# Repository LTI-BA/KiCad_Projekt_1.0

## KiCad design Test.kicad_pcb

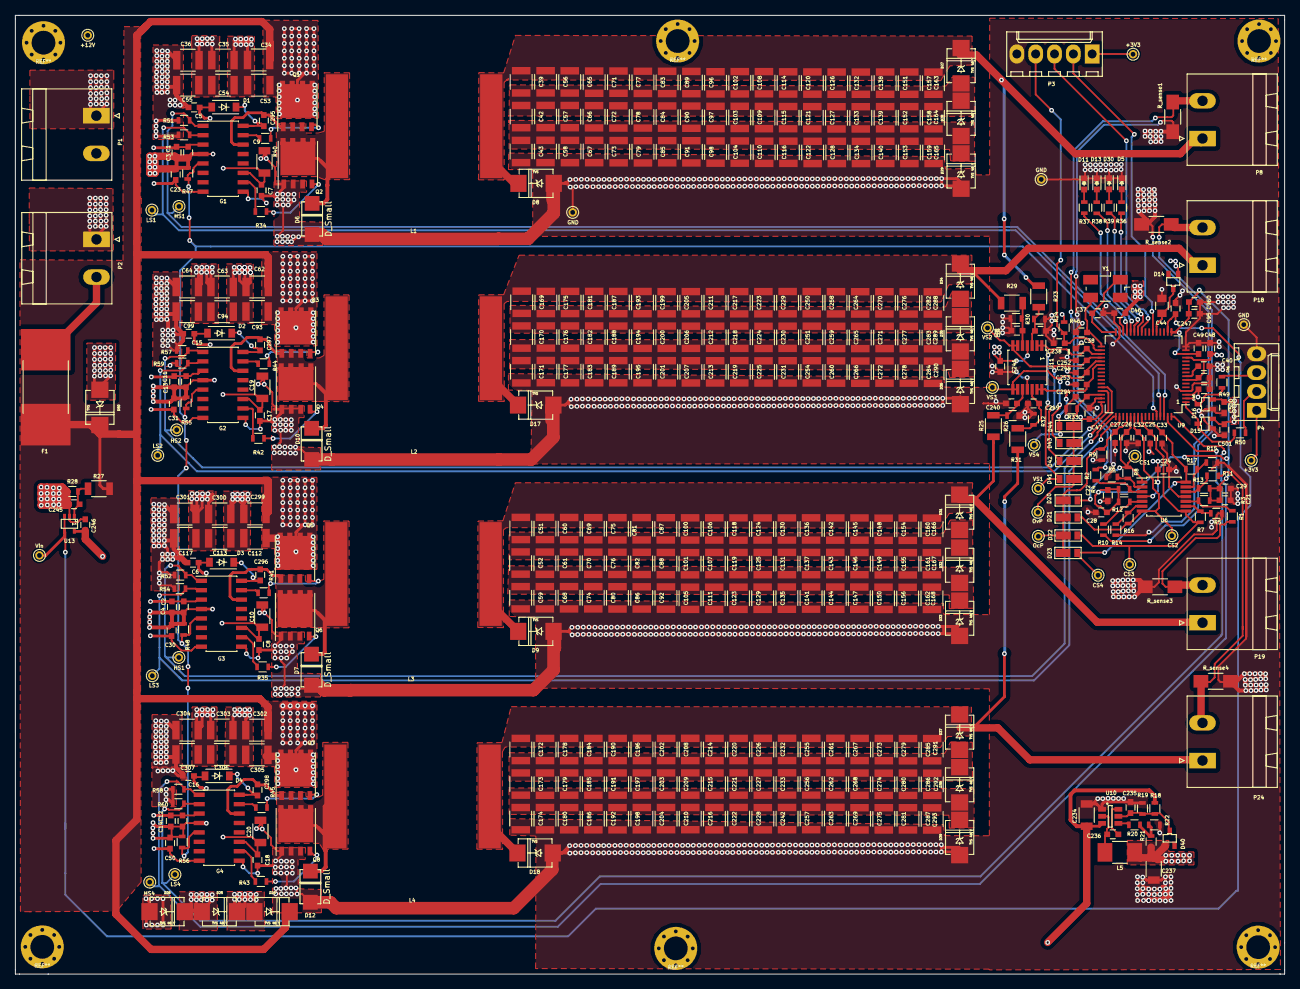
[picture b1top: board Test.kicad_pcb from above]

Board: 4 copper layers, 171.1 x 129.2 mm, 475 parts (0 on the bottom side), 105 nets.

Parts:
+3V3, +3V3#2, +12V: CONN_01X01; PINTST
C1, C2, C5, C6, C11, C12, C15, C16, C40, C41, C236: 1u; C_0603
C3, C4, C7, C8, C13, C14, C17, C18, C23, C24, C27, C30, C31, C45, C46, C47, C48, C49, C50, C95, C235, C238, C241, C246, C294, C295, C296, C297, C298, C500, C501: 100n; C_0603
C9, C10, C19, C20: 10u; C_1206
C21, C22, C28, C29, C239, C240, C245, C248, C249: 100p; C_0603
C25, C26, C32, C33, C243, C244, C247, C252, C253: 33p; C_0603
C34, C35, C36, C39, C42, C43, C51, C52, C53, C54, C55, C56, C57, C58, C59, C60, C61, C62, C63, C64, C65, C66, C67, C68, C69, C70, C71, C72, C73, C74, C75, C76, C77, C78, C79, C80, C81, C82, C83, C84, C85, C86, C87, C88, C89, C90, C91, C92, C93, C94, C96, C97, C98, C99, C100, C101, C102, C103, C104, C105, C106, C107, C108, C109, C110, C111, C112, C113, C114, C115, C116, C117, C118, C119, C120, C121, C122, C123, C124, C125, C126, C127, C128, C129, C130, C131, C132, C133, C134, C135, C136, C137, C138, C139, C140, C141, C142, C143, C144, C145, C146, C147, C148, C149, C150, C151, C152, C153, C154, C155, C156, C157, C158, C159, C160, C161, C162, C163, C164, C165, C166, C167, C168, C169, C170, C171, C172, C173, C174, C175, C176, C177, C178, C179, C180, C181, C182, C183, C184, C185, C186, C187, C188, C189, C190, C191, C192, C193, C194, C195, C196, C197, C198, C199, C200, C201, C202, C203, C204, C205, C206, C207, C208, C209, C210, C211, C212, C213, C214, C215, C216, C217, C218, C219, C220, C221, C222, C223, C224, C225, C226, C227, C228, C229, C230, C231, C232, C233, C242, C250, C251, C254, C255, C256, C257, C258, C259, C260, C261, C262, C263, C264, C265, C266, C267, C268, C269, C270, C271, C272, C273, C274, C275, C276, C277, C278, C279, C280, C281, C282, C283, C284, C285, C286, C287, C288, C289, C290, C291, C292, C293, C299, C300, C301, C302, C303, C304, C305, C306, C307: 10u; C_1210
C37, C38: 18p; C_0603
C44: 47u; C_0805
C234, C237: 22u; C_1206
C960: 10u; C_0603
CS1, CS2, CS3, CS4: CONN_01X01; PINTST
D1, D2, D3, D4: D; SOD-123
D5: red; LED_0603
D6, D7, D10, D12: D_Small; SOD-106
D8, D9, D17, D18: TVS; DO-214AA
D11: yel; LED_0603
D13: grn; LED_0603
D14, D15, D16, D40: BAT54SW; SOT-323
D20, D21, D22, D23, D41, D42, D43, D44: RSX201VA-30; TUMD2
D24, D25, D26, D27, D28, D29, D31, D32, D33, D34, D35, D36, D37, D38, D39: TVS 48 V; DO-214AA_TVS_inp
D30: ble; LED_0603
D50: TVS; DO-214AA_TVS_inp
F1: Fuse; Fuse_462_Serie
G1, G2, G3, G4: Si8237; SOIC-16_3.9x9.9mm_Pitch1.27mm
GND: CONN_01X01; PINTST
GND#2, GND#3: CONN_01X01; PINTST
HS1, HS1#2, HS2, HS4: CONN_01X01; PINTST
L1, L2, L3, L4: 330u; 6000B
L5: 4u7; R_1210_HandSoldering
LS1, LS2, LS3, LS4: CONN_01X01; PINTST
OcP: CONN_01X01; PINTST
OvP: CONN_01X01; PINTST
P1, P2, P8, P18, P19, P24: CONN_01X02; PhoenixContact_MSTBA-G_02x5.08mm_Angled
P3: CONN_01X05; Molex_KK-6410-05_05x2.54mm_Straight
P4: CONN_01X04; Molex_KK-6410-04_04x2.54mm_Straight
Q1, Q2, Q3, Q4, Q5, Q6, Q7, Q8: BSC440N10NS3GATMA1; PG-TDSON-8_F
R1, R2, R10, R11: 68; R_0603
R3, R4, R12, R13: 130k; R_0603
R5, R6, R14, R15, R22: 13k; R_0603
R7, R8, R16, R17: 91k; R_0603
R9, R33, R46, R47, R48, R51, R52, R53, R54, R55, R56, R57, R58, R59, R60: 10k; R_0603
R18: 100k; R_0603
R19: 15k; R_0603
R20: 75k; R_0603
R21: 40k2; R_0603
R23, R25, R27, R29, R31: 1M; R_1206
R24, R26, R28, R30, R32: 7.5k; R_0603
R34, R35, R40, R41, R42, R43, R44, R45: 2; R_0603
R36, R37, R38, R39: 470; R_0603
R49, R50: 22; R_0603
R_sense1, R_sense2, R_sense3, R_sense4: 0.1; R_1206_HandSoldering
U6: TLV4316; TSSOP-14_4.4x5mm_Pitch0.65mm
U9: MK22FN512VLH12; LQFP-64_10x10mm_Pitch0.5mm
U10: AP65201; SOT-23-6
U11: TSV524A; TSSOP-14_4.4x5mm_Pitch0.65mm
U13: TSV521; SC-70-5
VS1, VS2, VS3, VS4: CONN_01X01; PINTST
Vin: CONN_01X01; PINTST
Y1: ABMM2-8.000MHZ-E2-T; Crystal_SMD_5032_4Pads

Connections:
+3V3: +3V3.1, +3V3#2.1, C1.1, C2.1, C3.1, C4.1, C11.1, C12.1, C13.1, C14.1, C23.1, C24.2, C30.1, C31.1, C41.1, C45.2, C46.2, C47.2, C48.2, C50.1, C237.1, C241.1, C246.1, C500.1, C501.1, D14.1, D15.2, D16.2, D40.1, G1.3, G1.8, G2.3, G2.8, G3.3, G3.8, G4.3, G4.8, L5.2, P3.1, P4.1, R21.1, R46.2, U6.4, U9.3, U9.7, U9.13, U9.30, U9.48, U11.4, U13.5
/SW1: C295.2, D6.1, G1.14, L1.1, Q1.1, Q1.2, Q1.3, Q2.5, Q2.6, Q2.7, Q2.8
/SW2: C297.2, D10.1, G2.14, L2.1, Q3.1, Q3.2, Q3.3, Q4.5, Q4.6, Q4.7, Q4.8
/SW3: C296.2, D7.1, G3.14, L3.1, Q5.1, Q5.2, Q5.3, Q6.5, Q6.6, Q6.7, Q6.8
/SW4: C298.2, D12.1, G4.14, L4.1, Q7.1, Q7.2, Q7.3, Q8.5, Q8.6, Q8.7, Q8.8
CMP0_IN1_Overcur_Prot: C27.1, D20.1, D21.1, D22.1, D23.1, OcP.1, R9.1, U9.52
CMP1_IN1_Overvoltage_Prot: C294.1, D41.1, D42.1, D43.1, D44.1, OvP.1, R33.1, U9.46
Curr_Sense_Shunt_1: P8.2, R2.2, R_sense1.1
Curr_Sense_Shunt_2: P18.2, R10.2, R_sense2.1
Curr_Sense_Shunt_3: P19.2, R1.2, R_sense3.1
Curr_Sense_Shunt_4: P24.2, R11.2, R_sense4.1
Disable: G1.5, G2.5, G3.5, G4.5, R47.1, R48.1, R55.1, R56.1, U9.60
GND: C1.2, C2.2, C3.2, C4.2, C5.2, C6.2, C7.2, C8.2, C9.2, C10.2, C11.2, C12.2, C13.2, C14.2, C15.2, C16.2, C17.2, C18.2, C19.2, C20.2, C21.2, C22.2, C23.2, C24.1, C25.2, C26.2, C27.2, C28.2, C29.2, C30.2, C31.2, C32.2, C33.2, C36.2, C37.2, C38.2, C40.2, C41.2, C43.2, C44.2, C45.1, C46.1, C47.1, C48.1, C49.1, C50.2, C55.2, C58.2, C59.2, C64.2, C67.2, C68.2, C73.2, C74.2, C79.2, C80.2, C85.2, C86.2, C91.2, C92.2, C95.2, C98.2, C99.2, C104.2, C105.2, C110.2, C111.2, C116.2, C117.2, C122.2, C123.2, C128.2, C129.2, C134.2, C135.2, C140.2, C141.2, C144.2, C147.2, C150.2, C153.2, C156.2, C159.2, C162.2, C165.2, C168.2, C171.2, C174.2, C177.2, C180.2, C183.2, C186.2, C189.2, C192.2, C195.2, C198.2, C201.2, C204.2, C207.2, C210.2, C213.2, C216.2, C219.2, C222.2, C225.2, C228.2, C231.2, C234.2, C235.2, C237.2, C238.1, C239.2, C240.2, C241.2, C242.2, C243.2, C244.2, C245.2, C246.2, C247.2, C248.2, C249.2, C252.2, C253.2, C254.2, C257.2, C260.2, C263.2, C266.2, C269.2, C272.2, C275.2, C278.2, C281.2, C284.2, C287.2, C290.2, C293.2, C294.2, C301.2, C304.2, C307.2, C500.2, C501.2, C960.2, D5.1, D6.2, D7.2, D8.1, D9.1, D10.2, D11.1, D12.2, D13.1, D15.1, D16.1, D17.1, D18.1, D26.2, D29.2, D30.1, D33.2, D36.2, D39.2, D50.2, G1.4, G1.9, G2.4, G2.9, G3.4, G3.9, G4.4, G4.9, GND.1, GND#2.1, GND#3.1, P1.1, P2.1, P3.5, P4.4, Q2.1, Q2.2, Q2.3, Q4.1, Q4.2, Q4.3, Q6.1, Q6.2, Q6.3, Q8.1, Q8.2, Q8.3, R5.2, R6.2, R9.2, R14.2, R15.2, R19.2, R22.2, R24.2, R26.2, R28.2, R30.2, R32.2, R33.2, R47.2, R48.2, R51.1, R52.1, R53.1, R54.1, R55.2, R56.2, R57.1, R58.1, R59.1, R60.1, R_sense1.2, R_sense2.2, R_sense3.2, R_sense4.2, U6.11, U9.4, U9.15, U9.16, U9.31, U9.47, U10.1, U11.11, U13.2
unnamed: C37.1, U9.32, Y1.1
unnamed: C38.1, U9.33, Y1.2
unnamed: C40.1, U9.8
unnamed: C44.1, D14.3, U9.21
unnamed: C51.2, C52.1, C60.2, C61.1, C69.2, C70.1, C75.2, C76.1, C81.2, C82.1, C87.2, C88.1, C100.2, C101.1, C106.2, C107.1, C118.2, C119.1, C124.2, C125.1, C130.2, C131.1, C136.2, C137.1, C142.2, C143.1, C145.2, C146.1, C148.2, C149.1, C154.2, C155.1, C160.2, C161.1, C166.2, C167.1, D31.2, D32.1
unnamed: C52.2, C59.1, C61.2, C68.1, C70.2, C74.1, C76.2, C80.1, C82.2, C86.1, C88.2, C92.1, C101.2, C105.1, C107.2, C111.1, C119.2, C123.1, C125.2, C129.1, C131.2, C135.1, C137.2, C141.1, C143.2, C144.1, C146.2, C147.1, C149.2, C150.1, C155.2, C156.1, C161.2, C162.1, C167.2, C168.1, D32.2, D33.1
unnamed: C39.2, C42.1, C56.2, C57.1, C65.2, C66.1, C71.2, C72.1, C77.2, C78.1, C83.2, C84.1, C89.2, C90.1, C96.2, C97.1, C102.2, C103.1, C108.2, C109.1, C114.2, C115.1, C120.2, C121.1, C126.2, C127.1, C132.2, C133.1, C138.2, C139.1, C151.2, C152.1, C157.2, C158.1, C163.2, C164.1, D27.2, D28.1
unnamed: C42.2, C43.1, C57.2, C58.1, C66.2, C67.1, C72.2, C73.1, C78.2, C79.1, C84.2, C85.1, C90.2, C91.1, C97.2, C98.1, C103.2, C104.1, C109.2, C110.1, C115.2, C116.1, C121.2, C122.1, C127.2, C128.1, C133.2, C134.1, C139.2, C140.1, C152.2, C153.1, C158.2, C159.1, C164.2, C165.1, D28.2, D29.1
unnamed: C34.2, C35.1, C53.2, C54.1, C62.2, C63.1, C93.2, C94.1, C112.2, C113.1, C299.2, C300.1, C302.2, C303.1, C305.2, C306.1, D24.2, D25.1
unnamed: C35.2, C36.1, C54.2, C55.1, C63.2, C64.1, C94.2, C99.1, C113.2, C117.1, C300.2, C301.1, C303.2, C304.1, C306.2, C307.1, D25.2, D26.1
unnamed: C169.2, C170.1, C175.2, C176.1, C181.2, C182.1, C187.2, C188.1, C193.2, C194.1, C199.2, C200.1, C205.2, C206.1, C211.2, C212.1, C217.2, C218.1, C223.2, C224.1, C229.2, C230.1, C250.2, C251.1, C258.2, C259.1, C264.2, C265.1, C270.2, C271.1, C276.2, C277.1, C282.2, C283.1, C288.2, C289.1, D34.2, D35.1
unnamed: C170.2, C171.1, C176.2, C177.1, C182.2, C183.1, C188.2, C189.1, C194.2, C195.1, C200.2, C201.1, C206.2, C207.1, C212.2, C213.1, C218.2, C219.1, C224.2, C225.1, C230.2, C231.1, C251.2, C254.1, C259.2, C260.1, C265.2, C266.1, C271.2, C272.1, C277.2, C278.1, C283.2, C284.1, C289.2, C290.1, D35.2, D36.1
unnamed: C172.2, C173.1, C178.2, C179.1, C184.2, C185.1, C190.2, C191.1, C196.2, C197.1, C202.2, C203.1, C208.2, C209.1, C214.2, C215.1, C220.2, C221.1, C226.2, C227.1, C232.2, C233.1, C255.2, C256.1, C261.2, C262.1, C267.2, C268.1, C273.2, C274.1, C279.2, C280.1, C285.2, C286.1, C291.2, C292.1, D37.2, D38.1
unnamed: C173.2, C174.1, C179.2, C180.1, C185.2, C186.1, C191.2, C192.1, C197.2, C198.1, C203.2, C204.1, C209.2, C210.1, C215.2, C216.1, C221.2, C222.1, C227.2, C228.1, C233.2, C242.1, C256.2, C257.1, C262.2, C263.1, C268.2, C269.1, C274.2, C275.1, C280.2, C281.1, C286.2, C287.1, C292.2, C293.1, D38.2, D39.1
unnamed: C235.1, D40.3, R18.2, R19.1, U10.5
unnamed: C236.1, U10.6
unnamed: C236.2, L5.1, U10.2
unnamed: C239.1, R23.2, R24.1, U11.3
unnamed: C240.1, R25.2, R26.1, U11.10
unnamed: C245.1, R27.2, R28.1, U13.1
unnamed: C248.1, R29.2, R30.1, U11.5
unnamed: C249.1, R31.2, R32.1, U11.12
unnamed: C295.1, D1.1, G1.16
unnamed: C296.1, D3.1, G3.16
unnamed: C297.1, D2.1, G2.16
unnamed: C298.1, D4.1, G4.16
unnamed: D5.2, R36.2
unnamed: D11.2, R37.2
unnamed: D13.2, R38.2
unnamed: D30.2, R39.2
unnamed: G1.10, R34.2
unnamed: G1.15, R40.2
unnamed: G2.10, R42.2
unnamed: G2.15, R44.2
unnamed: G3.10, R35.2
unnamed: G3.15, R41.2
unnamed: G4.10, R43.2
unnamed: G4.15, R45.2
unnamed: P4.2, R50.2
unnamed: P4.3, R49.2
unnamed: Q1.4, R40.1
unnamed: Q2.4, R34.1
unnamed: Q3.4, R44.1
unnamed: Q4.4, R42.1
unnamed: Q5.4, R41.1
unnamed: Q6.4, R35.1
unnamed: Q7.4, R45.1
unnamed: Q8.4, R43.1
unnamed: R1.1, R3.2, U6.10
unnamed: R2.1, R4.2, U6.3
unnamed: R5.1, R7.2, U6.9
unnamed: R6.1, R8.2, U6.2
unnamed: R10.1, R12.2, U6.5
unnamed: R11.1, R13.2, U6.12
unnamed: R14.1, R16.2, U6.6
unnamed: R15.1, R17.2, U6.13
unnamed: R20.1, R21.2, R22.1
unnamed: R20.2, U10.4
PWM_HS_1: G1.1, HS1.1, R51.2, U9.62
PWM_HS_2: G2.1, HS2.1, R57.2, U9.45
PWM_HS_3: G3.1, HS1#2.1, R52.2, U9.49
PWM_HS_4: G4.1, HS4.1, R58.2, U9.64
PWM_LS_1: G1.2, LS1.1, R53.2, U9.61
PWM_LS_2: G2.2, LS2.1, R59.2, U9.44
PWM_LS_3: G3.2, LS3.1, R54.2, U9.50
PWM_LS_4: G4.2, LS4.1, R60.2, U9.63
SWD_CLK: P3.2, U9.22
SWD_DIO_TGTMCU: P3.3, U9.25
SWD_RESET: C238.2, P3.4, R46.1, U9.34
Sense_Curr_1: C26.1, CS1.1, D20.2, R8.1, U6.1, U9.53
Sense_Curr_2: C32.1, CS2.1, D21.2, R16.1, U6.7, U9.54
Sense_Curr_3: C25.1, CS3.1, D22.2, R7.1, U6.8, U9.55
Sense_Curr_4: C33.1, CS4.1, D23.2, R17.1, U6.14, U9.56
Sense_Inp_Volt: C247.1, U9.18, U13.3, U13.4, Vin.1
Sense_Out_Volt_1: C243.1, D41.2, U9.35, U11.1, U11.2, VS1.1
Sense_Out_Volt_2: C252.1, D42.2, U9.36, U11.6, U11.7, VS2.1
Sense_Out_Volt_3: C244.1, D43.2, U9.37, U11.8, U11.9, VS3.1
Sense_Out_Volt_4: C253.1, D44.2, U9.38, U11.13, U11.14, VS4.1
UART1_RX: D16.3, R49.1, U9.2
UART1_TX: D15.3, R50.1, U9.1
V_12V: +12V.1, C5.1, C6.1, C7.1, C8.1, C9.1, C10.1, C15.1, C16.1, C17.1, C18.1, C19.1, C20.1, C234.1, D1.2, D2.2, D3.2, D4.2, G1.11, G2.11, G3.11, G4.11, P1.2, R18.1, U10.3
V_in+: F1.1, P2.2
V_in-: C34.1, C53.1, C62.1, C93.1, C112.1, C299.1, C302.1, C305.1, D24.1, D50.1, F1.2, Q1.5, Q1.6, Q1.7, Q1.8, Q3.5, Q3.6, Q3.7, Q3.8, Q5.5, Q5.6, Q5.7, Q5.8, Q7.5, Q7.6, Q7.7, Q7.8, R27.1
V_out_1: C39.1, C56.1, C65.1, C71.1, C77.1, C83.1, C89.1, C96.1, C102.1, C108.1, C114.1, C120.1, C126.1, C132.1, C138.1, C151.1, C157.1, C163.1, D8.2, D27.1, L1.2, P8.1, R23.1
V_out_2: C169.1, C175.1, C181.1, C187.1, C193.1, C199.1, C205.1, C211.1, C217.1, C223.1, C229.1, C250.1, C258.1, C264.1, C270.1, C276.1, C282.1, C288.1, D17.2, D34.1, L2.2, P18.1, R29.1
V_out_3: C51.1, C60.1, C69.1, C75.1, C81.1, C87.1, C100.1, C106.1, C118.1, C124.1, C130.1, C136.1, C142.1, C145.1, C148.1, C154.1, C160.1, C166.1, D9.2, D31.1, L3.2, P19.1, R25.1
V_out_4: C172.1, C178.1, C184.1, C190.1, C196.1, C202.1, C208.1, C214.1, C220.1, C226.1, C232.1, C255.1, C261.1, C267.1, C273.1, C279.1, C285.1, C291.1, D18.2, D37.1, L4.2, P24.1, R31.1
Vref: C21.1, C22.1, C28.1, C29.1, C49.2, C95.1, C960.1, R3.1, R4.1, R12.1, R13.1, U9.14, U9.17
led_ble: R39.1, U9.27
led_grn: R38.1, U9.28
led_red: R36.1, U9.26
led_yel: R37.1, U9.29

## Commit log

2016-09-01 Version 1.0
2016-09-02 Changed some Diodes footprints to achieve the recommended ones on the datasheet
2016-09-02 vias under Mosfets more cupper for GND general changes
